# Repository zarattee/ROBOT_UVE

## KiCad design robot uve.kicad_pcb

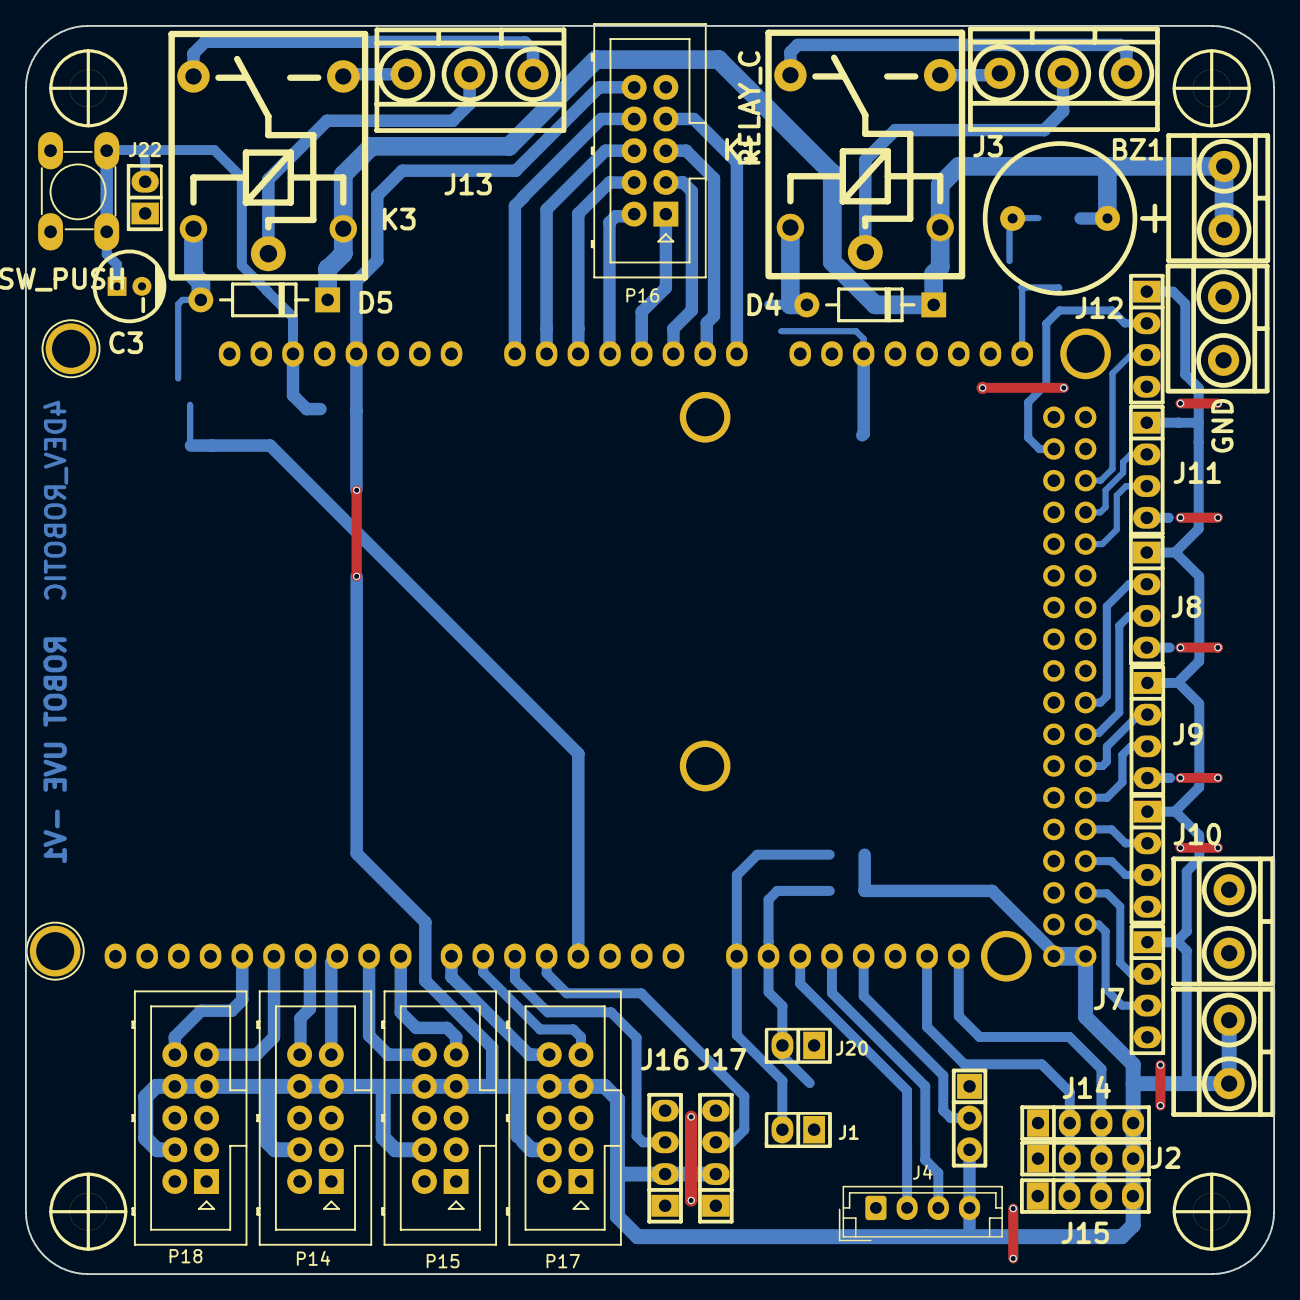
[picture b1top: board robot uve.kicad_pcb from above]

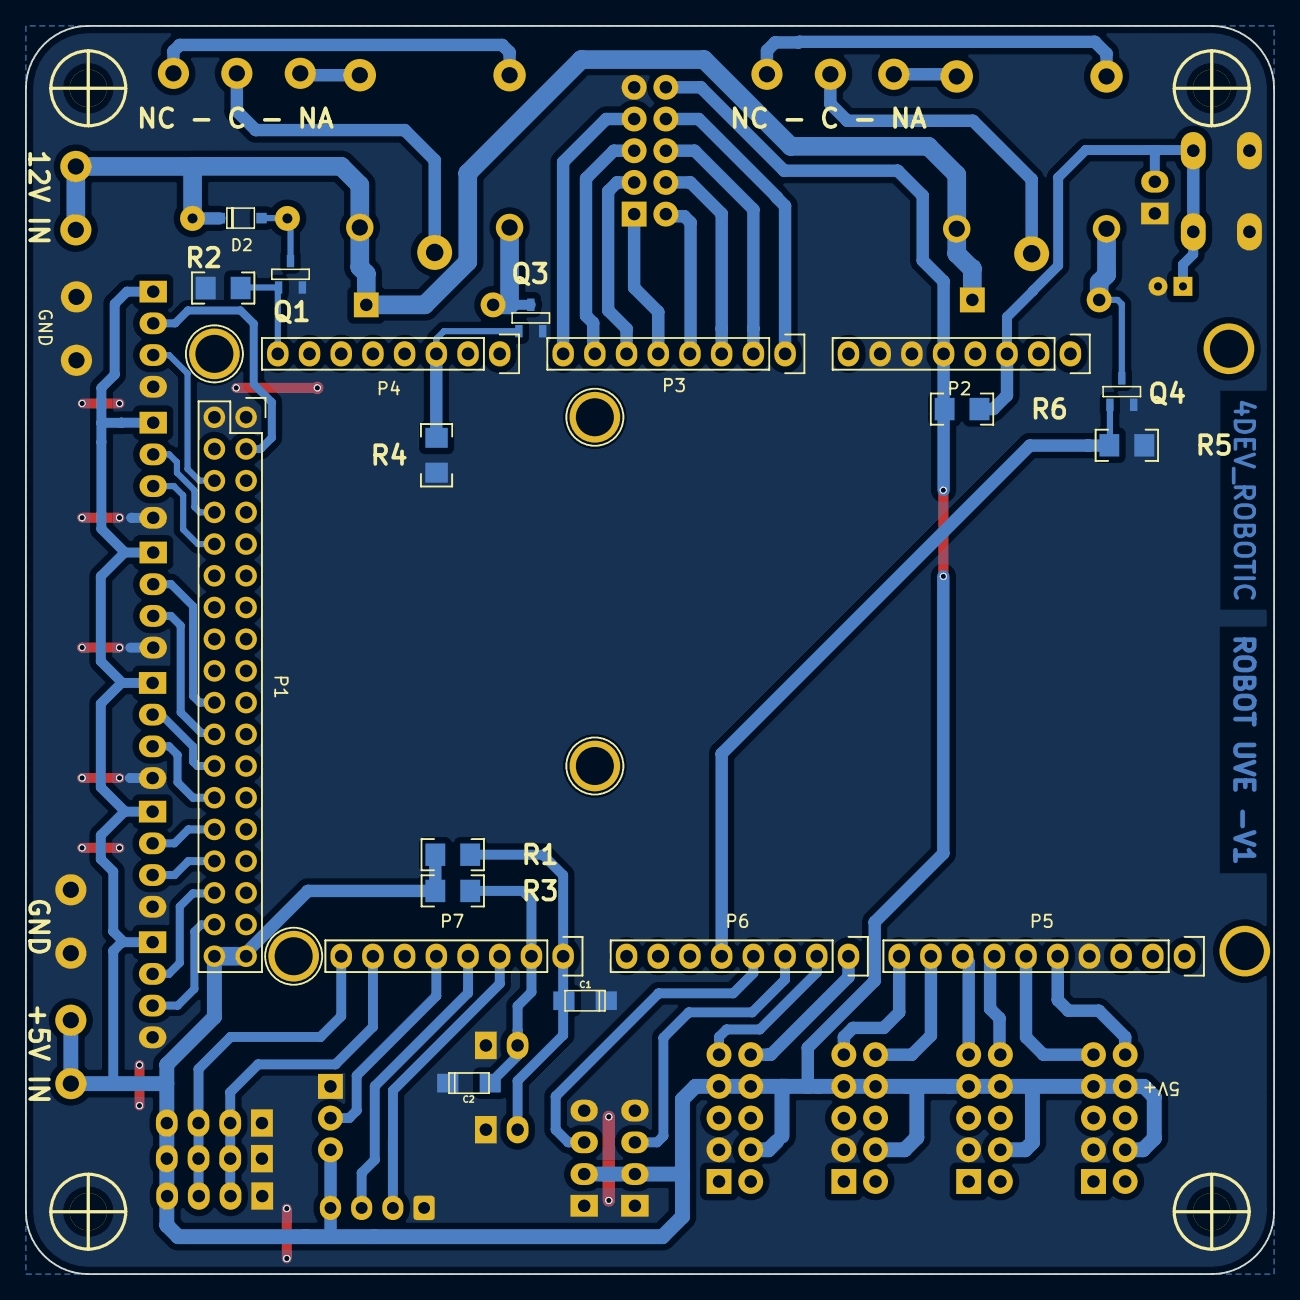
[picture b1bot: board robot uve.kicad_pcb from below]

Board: 2 copper layers, 100.0 x 100.0 mm, 63 parts (23 on the bottom side), 53 nets.

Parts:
BZ1: Buzzer; Buzzer_12mm
C1, C2: 10uf; CAP_TAN_A
C3: 10uf; CAP_ELEC_5x11mm
D2: 1N4148; sod123
D4, D5: 1N4148; DO-41
H1, H2, H3, H4: Mounting_Hole; hole_3mm
J1: pulsador1; Pin_Header_2
J2: I2C_A; pin_strip_4
J3, J13: NC - C - NA; BORNERA3_AZUL
J4: comunicacion a rpi; JST_EH_B4B-EH-A_1x04_P2.50mm_Vertical
J5: 12V IN; BORNERA2_AZUL
J6, J19: GND; BORNERA2_AZUL
J7, J8, J9, J10, J11, J12: HC-SR04; pin_strip_4
J14: I2C_B; pin_strip_4
J15: I2C_C; pin_strip_4
J16: NeoPixel; pin_strip_4
J17: neopixel; pin_strip_4
J18: +5V IN; BORNERA2_AZUL
J20: pulsador2; Pin_Header_2
J21: IR; Pin_Strip_3
J22: RST; Pin_Header_2
K1, K3: RELAY_C; Relay_C
P1: Digital; Socket_Strip_Arduino_2x18
P2: Power; Socket_Strip_Arduino_1x08
P3, P4: Analog; Socket_Strip_Arduino_1x08
P5: PWM; Socket_Strip_Arduino_1x10
P6: PWM; Socket_Strip_Arduino_1x08
P7: Communication; Socket_Strip_Arduino_1x08
P8, P9, P10, P11, P12, P13: CONN_01X01; Arduino_1pin
P14: motor3; Header_2x05x2.54mm_Vertical
P15: motor2; Header_2x05x2.54mm_Vertical
P16: Sensores de Linea; Header_2x05x2.54mm_Vertical
P17: motor1; Header_2x05x2.54mm_Vertical
P18: motor4; Header_2x05x2.54mm_Vertical
Q1, Q3, Q4: 2N7002; SOT23
R1, R3, R6: 10k; R_1206
R2, R4, R5: 10K; R_1206
SW1: SW_PUSH; Pulsador_TH_4

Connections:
+5V: J2.4, J4.4, J7.1, J8.1, J9.1, J10.1, J11.1, J12.1, J14.4, J15.4, J16.2, J17.2, J18.1, J18.2, J21.3, P1.35, P1.36, P2.5, P14.4, P14.7, P14.8, P15.4, P15.7, P15.8, P16.10, P17.4, P17.7, P17.8, P18.4, P18.7, P18.8, R1.1, R3.1, R6.1
/3(**): P6.5, Q4.1, R5.1
/4(**): J17.3, P6.4
/5(**): J16.3, P6.3
/6(**): P6.2, P17.9
/7(**): P6.1, P17.10
/8(**): P5.10, P15.9
/9(**): P5.9, P15.10
/10(**): P5.8, P14.9
/11(**): P5.7, P14.10
/12(**): P5.6, P18.9
/12V: BZ1.1, D2.2, D4.2, D5.2, J5.1, J5.2, K1.2, K3.2
/13(**): P5.5, P18.10
/14(Tx3): C1.1, J1.2, P7.1, R1.2
/15(Rx3): C2.1, J20.2, P7.2, R3.2
/16(Tx2): J4.2, P7.3
/17(Rx2): J4.3, P7.4
/18(Tx1): J21.2, P7.5
/20(SDA): J2.2, J14.2, J15.2, P7.7
/21(SCL): J2.3, J14.3, J15.3, P7.8
/23: J7.3, P1.34
/25: J7.2, P1.32
/27: J10.3, P1.30
/29: J10.2, P1.28
/31: J9.3, P1.26
/33: J9.2, P1.24
/35: J8.3, P1.22
/37: J8.2, P1.20
/47: J11.3, P1.10
/49: J11.2, P1.8
/51(MOSI): J12.3, P1.6
/52(SCK): J12.2, P1.3
/A0: P3.1, P16.8
/A1: P3.2, P16.6
/A2: P3.3, P16.4
/A3: P3.4, P16.2
/A4: P3.5, P16.1
/A5: P3.6, P16.3
/A6: P3.7, P16.5
/A7: P3.8, P16.7
/A10: P4.3, Q3.1, R4.1
/A15: P4.8, Q1.1, R2.1
/Reset: C3.1, J22.2, P2.3, R6.2, SW1.3, SW1.4
GND: C1.2, C2.2, C3.2, J1.1, J2.1, J4.1, J6.1, J6.2, J7.4, J8.4, J9.4, J10.4, J11.4, J12.4, J14.1, J15.1, J16.1, J16.4, J17.1, J17.4, J19.1, J19.2, J20.1, J21.1, J22.1, P1.1, P1.2, P2.6, P2.7, P5.4, P14.3, P15.3, P16.9, P17.3, P18.3, Q1.3, Q3.3, Q4.3, R2.2, R4.2, R5.2, SW1.1, SW1.2
unnamed: BZ1.2, D2.1, Q1.2
unnamed: D4.1, K1.5, Q3.2
unnamed: D5.1, K3.5, Q4.2
unnamed: J3.1, K1.4
unnamed: J3.2, K1.1
unnamed: J3.3, K1.3
unnamed: J13.1, K3.4
unnamed: J13.2, K3.1
unnamed: J13.3, K3.3

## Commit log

2020-11-27 SE AGREGA ARCHIVOS DE FABRICACION
    se acomo los archivos a sus carpetas y se agrego los archicos de fabricacion
2020-11-27 Actualización modelo 3D
    Ajuste el modelo 3D de los conectores de cable plano 2x5 para los drivers de motores
2020-11-27 se modifico archicos de fabricacion
    se modifico archivos de fabricaciony se mejoro el pcb
2020-11-30 modificacion en el pcb
    se modifico el pcb
    se agrego boton reset
    se modifico seregrafia
    se modifico vias
    y se agrego archicos BOM
2020-11-30 Varios
    Pase a SMD (1206) las resistencias.
    Modifique una conexión a 5V para evitar un jumper.
    Acomode un poco más la serigrafia (todavía falta).
2020-12-01 varios cambios
    se agrega lista de componentes
    se modifica el pcb
2020-12-01 LISTA DE COMPONENTES
    SE MODIFICO LISTA DE COMPONENTES
2020-12-01 Img Pinout + avances en pcb
    Agregue la imagen del pinout del arduino Mega en el sch, esta en una escala muy baja para que no moleste, en caso de necesitar revisar algo, cambiar la escala y luego volverla a la actual.
    Cambie el icono del rotulo de SCH.
    Movi un SOT-23 para que el poligono de GND pueda pasar por debajo del relay y evitar un jumper.
2020-12-01 MODIFICACIONES
    se modifico pcb
    se movio los conectores para eviar 2 vias mas
    se cambio de huella pin_strip_4 a JST_4
    al conectior de comunicacion a rpi
    se esta armando la lista de componentes
    se modifico el SCH para que reorganizar el ruteo del pcb
2020-12-02 Reasignación de pines y layout
    Cambié la conexion del control IR, de la comunicacion serie hacia la RPI.
    Cambié el footprint de los capacitores de los pulsadores y redibuje el pcb para contemplar los cambios
2020-12-02 VCC width
    Cambié el ancho de la pista de alimentación
2020-12-02 Alineación de vias
    Acomode las vias de GND del lateral derecho y genere el archivo para la fabricacion casera.
2020-12-03 actualizacion de lista de componentes
    se agrago precios de algunos componentes en la lista de componetes
